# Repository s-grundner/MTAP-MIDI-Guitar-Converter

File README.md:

# [MTAP-MIDI-Guitar-Converter](http://www.htl-salzburg.ac.at/elektronik-technische-informatik-diplomarbeiten/1594.html) [DE]
<picture>
 <source media="(prefers-color-scheme: dark)" srcset="/documentation/images/MTAP-logo-weiss.png" align="right" width="450px"/>
 
</picture>

## Kurzberschreibung
Das vorliegende Projekt ermöglicht die Verwendung einer E-Gitarre als MIDI-Device. Das Gerät soll einzelne Noten und Akkorde zuverlässig mit möglichst geringer Latenz in das MIDI-Format umwandeln. Die MIDI-Signale werden an die USB-Schnittstelle eines PCs übertragen, von welchem die Signale beliebig interpretiert werden können.

## Vorhaben, Lösungsweg und Innovation
Virtuelle Instrumente sind in der modernen Musik-Produktion aufgrund ihrer Vielseitigkeit weit verbreitet. Das Projekt, ein Audiodaten-Verarbeitungssystem, macht es möglich, diese virtuellen Instrumente auch mit einer E-Gitarre zu spielen. Hierfür wird das analoge Audiosignal direkt von der Ausgangsbuchse der Gitarre abgegriffen, in MIDI-Noten umgewandelt und via USB an eine Digital Audio Workstation (DAW) übertragen.

Die Ein- und Ausgänge des Systems umfassen eine Micro-USB-Buchse und zwei Mono-Audio Buchsen. Die analogen Signale werden zunächst an einer der Buchsen abgegriffen, digitalisiert und von einem leistungsstarken 32-Bit Prozessor analysiert. Die Daten, die sich aus der Analyse ergeben, werden anschließend in das MIDI Format konvertiert und über die USB-Schnittstelle ausgegeben.

Der Vorteil des MIDI-Formats ist, dass es der Standard vieler Musikproduktionsumgebungen ist. In der DAW wird das MIDI-Signal als Note auf einem Klavier interpretiert, welches dann in beliebige virtuelle Instrumente eingespeist werden kann und somit einen benutzerdefinierten Ton abspielt.

### 3D Renderung der Platine

| Top-Seite | Bot-Seite |
|-|-|
|||

### Assemblierter Prototyp

|  |  |
|-|-|

## Mitwirkende
### Betreuer
[Prof. Dipl.-Ing. Siegbert Schrempf](https://www.linkedin.com/in/siegbert-schrempf-aa1189a)
### Entwickler
- [Simon Grundner](https://github.com/s-grundner)
- [Laurenz Hölzl](https://github.com/Laurenz03)
- [Daniel Bräumann](https://github.com/Hexewillfred)

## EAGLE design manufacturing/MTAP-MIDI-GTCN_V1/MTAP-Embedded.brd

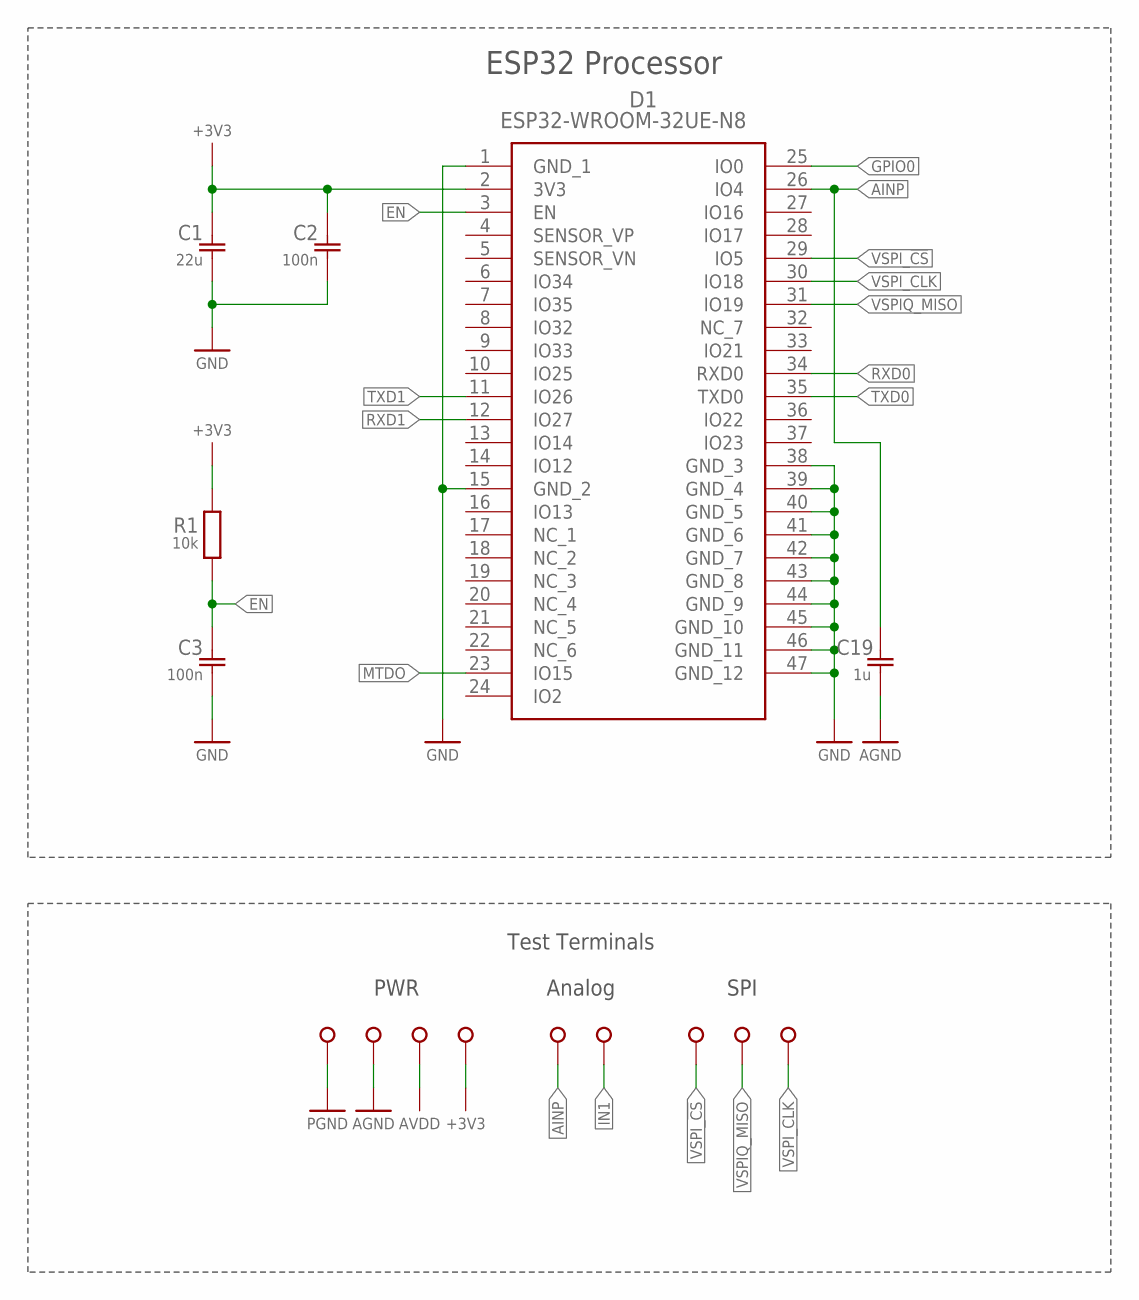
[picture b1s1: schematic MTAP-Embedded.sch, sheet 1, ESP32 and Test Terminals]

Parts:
3V3: SMD-TP; S2751-46R
AGND: SMD-TP; S2751-46R
AIN: SMD-TP; S2751-46R
AVDD: SMD-TP; S2751-46R
C1: 22u; C0805
C2, C3: 100n; C0805
C19: 1u; C0805
D1: ESP32-WROOM-32UE-N8; ESP32WROOM32UEN8
PGND: SMD-TP; S2751-46R
POST-AFE: SMD-TP; S2751-46R
R1: 10k; R0805
SPIQ: SMD-TP; S2751-46R
SPI_CLK: SMD-TP; S2751-46R
SPI_CS: SMD-TP; S2751-46R

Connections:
+3V3: 3V3.P$1, C1.1, C2.1, D1.2 (3V3), R1.2; also elsewhere on the board
AGND: AGND.P$1, C19.2; also elsewhere on the board
AINP: C19.1, D1.26 (IO4), POST-AFE.P$1; also elsewhere on the board
AVDD: AVDD.P$1; also elsewhere on the board
EN: C3.1, D1.3 (EN), R1.1; also elsewhere on the board
GND: C1.2, C2.2, C3.2, D1.1 (GND_1), D1.15 (GND_2), D1.38 (GND_3), D1.39 (GND_4), D1.40 (GND_5), D1.41 (GND_6), D1.42 (GND_7), D1.43 (GND_8), D1.44 (GND_9), D1.45 (GND_10), D1.46 (GND_11), D1.47 (GND_12); also elsewhere on the board
GPIO0: D1.25 (IO0); also elsewhere on the board
IN1: AIN.P$1; also elsewhere on the board
MTDO: D1.23 (IO15)
PGND: PGND.P$1; also elsewhere on the board
RXD0: D1.34 (RXD0); also elsewhere on the board
RXD1: D1.12 (IO27); also elsewhere on the board
TXD0: D1.35 (TXD0); also elsewhere on the board
TXD1: D1.11 (IO26); also elsewhere on the board
VSPIQ_MISO: D1.31 (IO19), SPIQ.P$1; also elsewhere on the board
VSPI_!CS: D1.29 (IO5), SPI_CS.P$1; also elsewhere on the board
VSPI_CLK: D1.30 (IO18), SPI_CLK.P$1; also elsewhere on the board

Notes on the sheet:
ESP32 Processor
PWR
Analog
SPI
Test Terminals

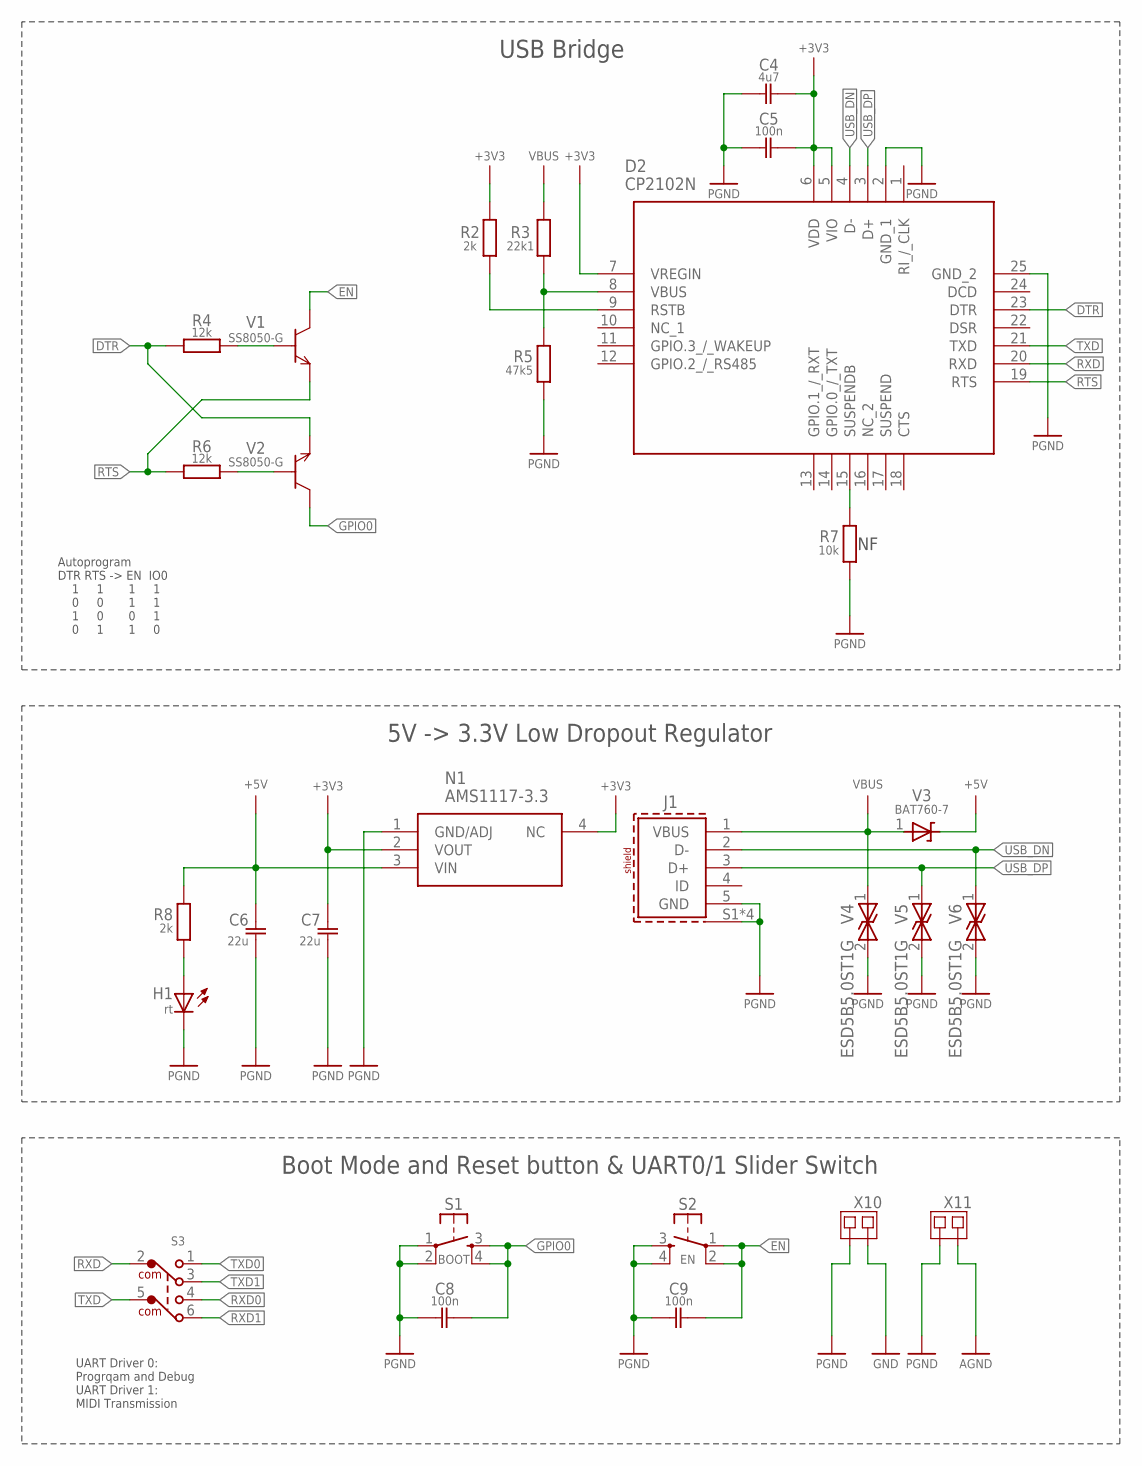
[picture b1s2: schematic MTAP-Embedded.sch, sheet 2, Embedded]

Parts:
C4: 4u7; C0805
C5, C8, C9: 100n; C0805
C6, C7: 22u; C0805
D2: CP2102N; QFN24
H1: rt; CHIP-LED0805
J1: 629105150521
N1: AMS1117-3.3; SOT229P700X180-4N
R2, R8: 2k; R0805
R3: 22k1; R0805
R4, R6: 12k; R0805
R5: 47k5; R0805
R7: 10k; R0805
S1: BOOT; WE_436331045822
S2: EN; WE_436331045822
S3: 452404020202
V1, V2: SS8050-G; SOT95P240X115-3N
V3: BAT760-7; SOD323
V4, V5, V6: ESD5B5.0ST1G; SOD523
X10, X11: 0R; MYLIB_SJ-SHORT

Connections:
+3V3: C4.1, C5.1, C7.1, D2.5 (VIO), D2.6 (VDD), D2.7 (VREGIN), N1.2 (VOUT), N1.4 (NC), R2.1; also elsewhere on the board
+5V: C6.1, N1.3 (VIN), R8.2, V3.2 (A)
AGND: X11.2; also elsewhere on the board
DTR: D2.23 (DTR), R4.1, V2.2 (E)
EN: C9.1, S2.1, S2.2 (P1), V1.3 (C); also elsewhere on the board
GND: X10.2; also elsewhere on the board
GPIO0: C8.1, S1.3 (S), S1.4 (S1), V2.3 (C); also elsewhere on the board
unnamed: H1.A, R8.1
unnamed: D2.8 (VBUS), R3.2, R5.2
unnamed: D2.15 (SUSPENDB), R7.2
unnamed: D2.9 (RSTB), R2.2
unnamed: R4.2, V1.1 (B)
unnamed: R6.2, V2.1 (B)
PGND: C4.2, C5.2, C6.2, C7.2, C8.2, C9.2, D2.2 (GND_1), D2.25 (GND_2), H1.C, J1.5 (GND), J1.S1 (SHIELD), J1.S2 (SHIELD), J1.S3 (SHIELD), J1.S4 (SHIELD), N1.1 (GND/ADJ), R5.1, R7.1, S1.1, S1.2 (P1), S2.3 (S), S2.4 (S1), V4.2, V5.2, V6.2, X10.1, X11.1; also elsewhere on the board
RTS: D2.19 (RTS), R6.1, V1.2 (E)
RXD: D2.20 (RXD), S3.2 (COM)
RXD0: S3.4; also elsewhere on the board
RXD1: S3.6; also elsewhere on the board
TXD: D2.21 (TXD), S3.5 (COM1)
TXD0: S3.1; also elsewhere on the board
TXD1: S3.3; also elsewhere on the board
USB_DN: D2.4 (D-), J1.2 (D-), V6.1
USB_DP: D2.3 (D+), J1.3 (D+), V5.1
VBUS: J1.1 (VBUS), R3.1, V3.1 (K), V4.1

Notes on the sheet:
UART Driver 0: Progrqam and Debug UART Driver 1: MIDI Transmission
USB Bridge
5V -> 3.3V Low Dropout Regulator
Boot Mode and Reset button & UART0/1 Slider Switch
Autoprogram DTR RTS -> EN IO0 1 1 1 1 0 0 1 1 1 0 0 1 0 1 1 0

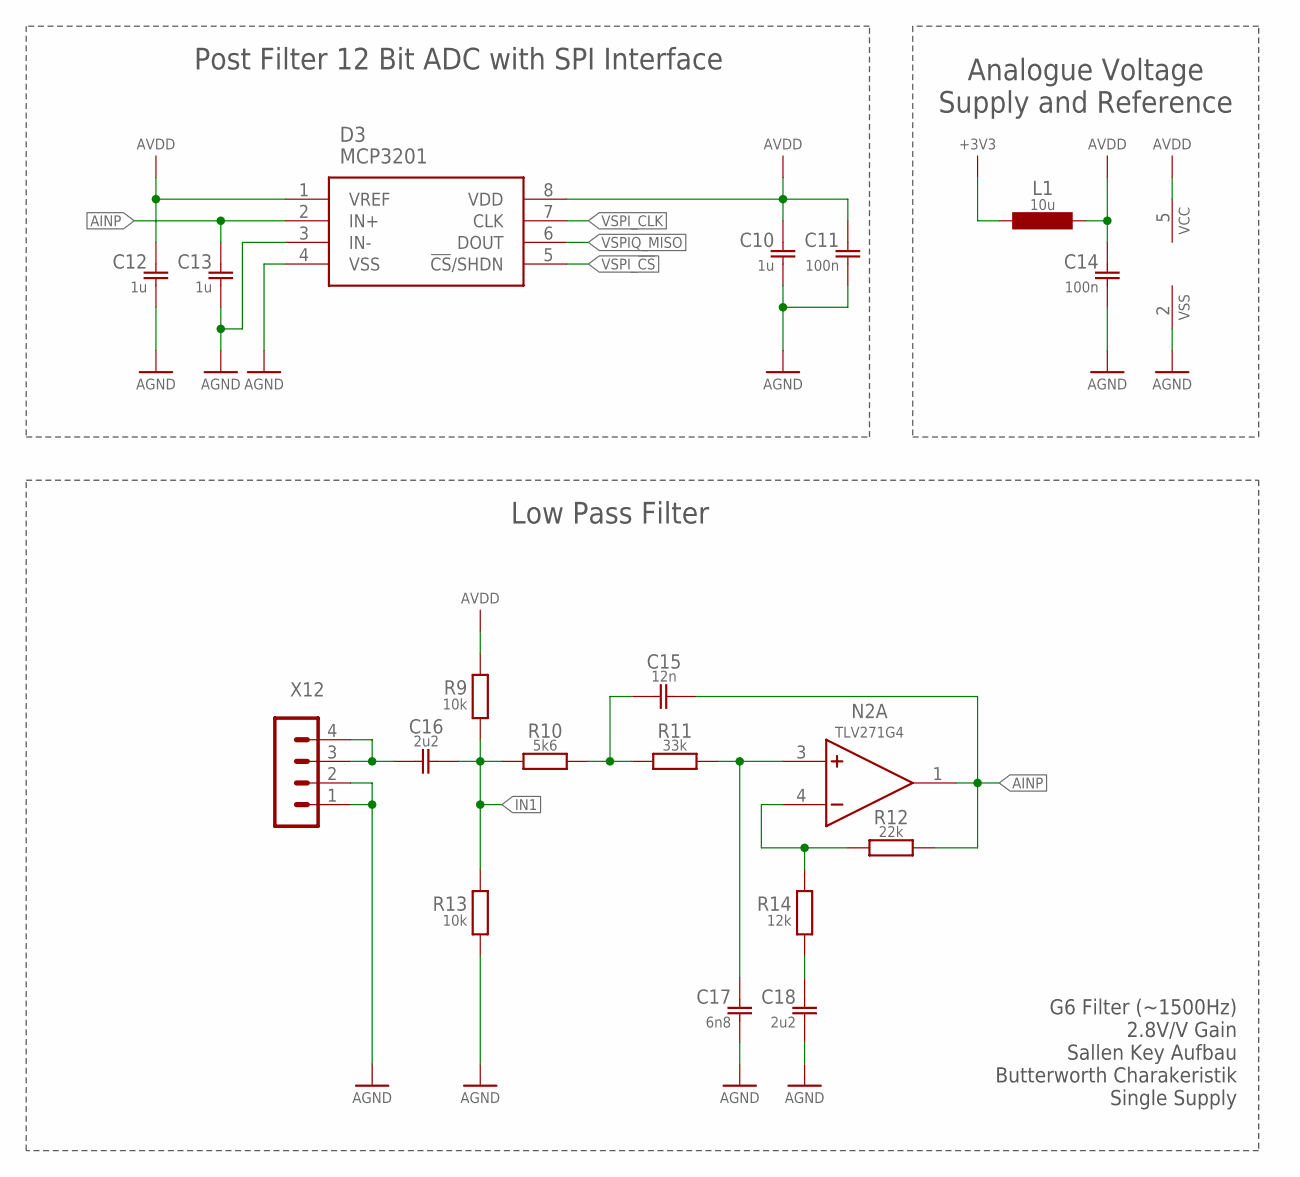
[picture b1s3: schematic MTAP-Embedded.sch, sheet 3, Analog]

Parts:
C10, C12, C13: 1u; C0805
C11, C14: 100n; C0805
C15: 12n; C0805
C16, C18: 2u2; C0805
C17: 6n8; C0805
D3: MCP3201; SOIC127P600X175-8N
L1: 10u; MYLIB_L3216C
N2: TLV271G4; SOT95P280X145-5N
R9, R13: 10k; R0805
R10: 5k6; R0805
R11: 33k; R0805
R12: 22k; R0805
R14: 12k; R0805
X12: MA04-1

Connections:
+3V3: L1.1; also elsewhere on the board
AGND: C10.2, C11.2, C12.2, C13.2, C14.2, C17.2, C18.2, D3.3 (IN-), D3.4 (VSS), N2.2 (VSS), R13.1, X12.1, X12.2; also elsewhere on the board
AINP: C13.1, C15.1, D3.2 (IN+), N2.1 (O), R12.2; also elsewhere on the board
AVDD: C10.1, C11.1, C12.1, C14.1, D3.1 (VREF), D3.8 (VDD), L1.2, N2.5 (VCC), R9.2; also elsewhere on the board
IN0: C16.2, X12.3, X12.4
IN1: C16.1, R9.1, R10.1, R13.2; also elsewhere on the board
unnamed: N2.4 (N), R12.1, R14.2
unnamed: C18.1, R14.1
unnamed: C17.1, N2.3, R11.2
unnamed: C15.2, R10.2, R11.1
VSPIQ_MISO: D3.6 (DOUT); also elsewhere on the board
VSPI_!CS: D3.5 (!CS!/SHDN); also elsewhere on the board
VSPI_CLK: D3.7 (CLK); also elsewhere on the board

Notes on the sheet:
Post Filter 12 Bit ADC with SPI Interface
Analogue Voltage Supply and Reference
Low Pass Filter
G6 Filter (~1500Hz) 2.8V/V Gain Sallen Key Aufbau Butterworth Charakeristik Single Supply

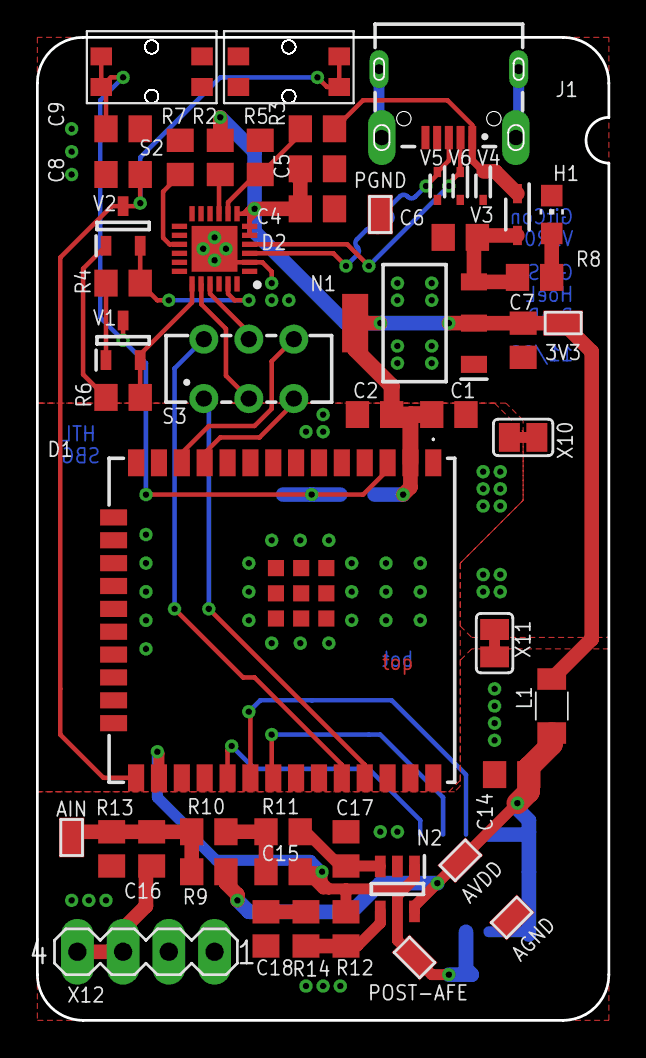
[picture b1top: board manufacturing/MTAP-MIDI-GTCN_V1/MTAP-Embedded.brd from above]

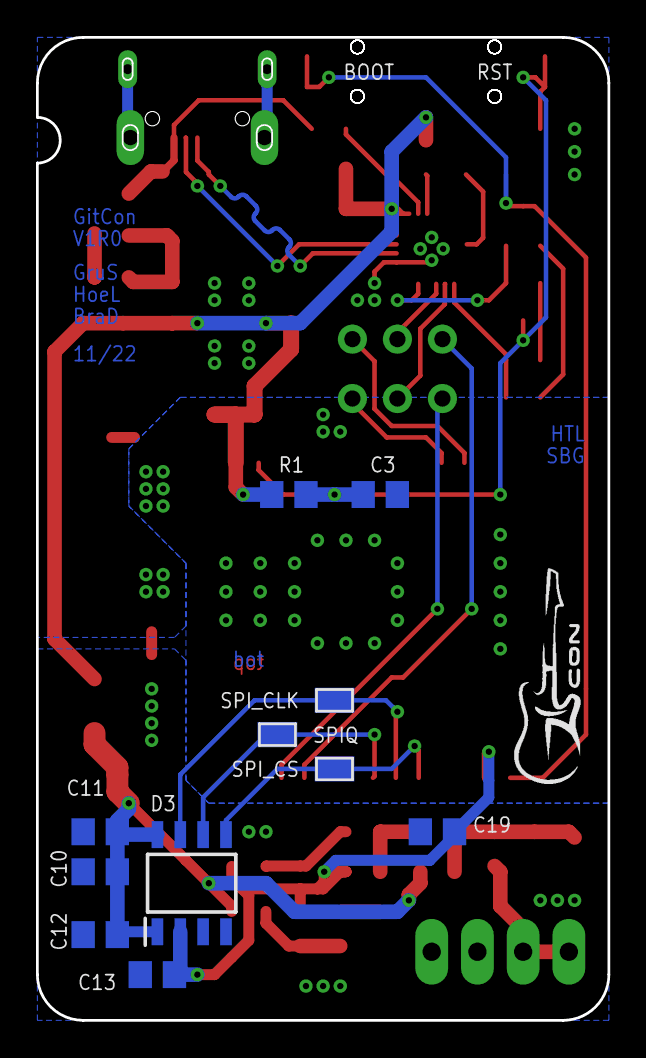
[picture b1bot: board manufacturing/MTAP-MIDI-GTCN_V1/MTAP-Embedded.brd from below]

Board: 2 copper layers, 31.8 x 54.6 mm, 64 parts (11 on the bottom side), 35 nets.

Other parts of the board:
FABRICATION: FABRIACTION
MEASURE: MEASURE

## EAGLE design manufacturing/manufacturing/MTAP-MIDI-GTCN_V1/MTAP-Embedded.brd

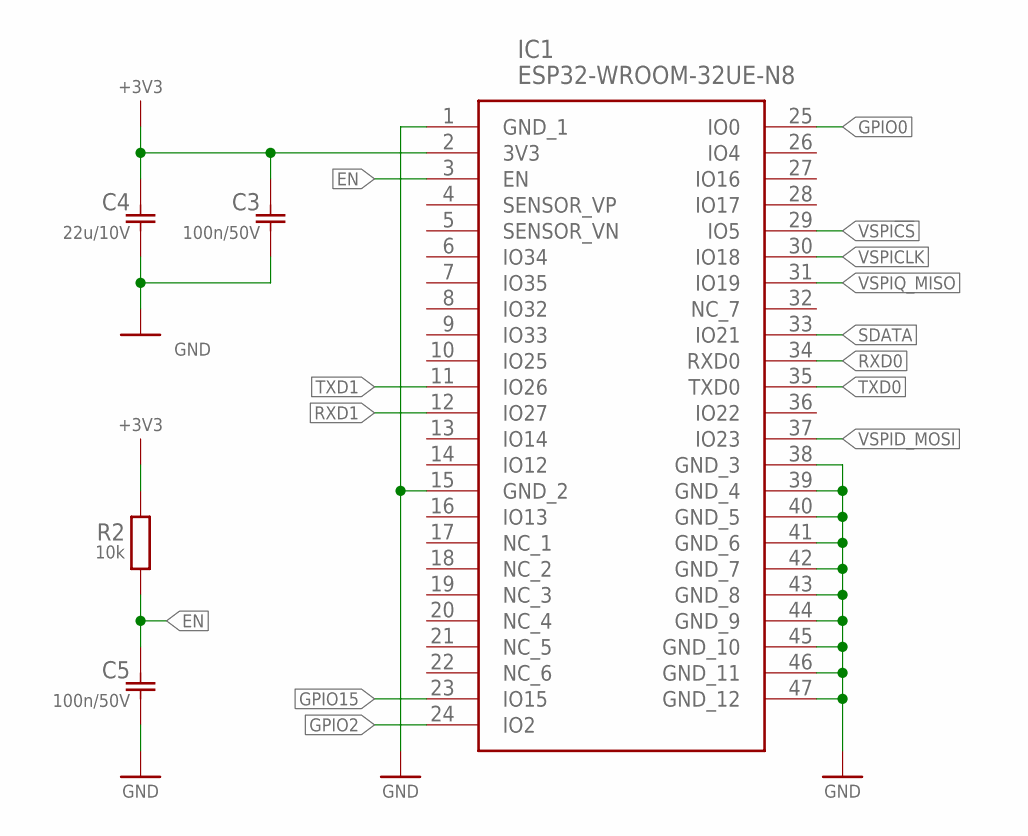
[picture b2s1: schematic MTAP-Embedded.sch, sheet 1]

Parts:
C3, C5: 100n/50V; C0805
C4: 22u/10V; C0805
IC1: ESP32-WROOM-32UE-N8; ESP32WROOM32UEN8
R2: 10k; R0805

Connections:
+3V3: C3.1, C4.1, IC1.2 (3V3), R2.2; also elsewhere on the board
EN: C5.1, IC1.3 (EN), R2.1; also elsewhere on the board
GND: C3.2, C4.2, C5.2, IC1.1 (GND_1), IC1.15 (GND_2), IC1.38 (GND_3), IC1.39 (GND_4), IC1.40 (GND_5), IC1.41 (GND_6), IC1.42 (GND_7), IC1.43 (GND_8), IC1.44 (GND_9), IC1.45 (GND_10), IC1.46 (GND_11), IC1.47 (GND_12); also elsewhere on the board
GPIO0: IC1.25 (IO0); also elsewhere on the board
GPIO2: IC1.24 (IO2)
GPIO15: IC1.23 (IO15)
RXD0: IC1.34 (RXD0); also elsewhere on the board
RXD1: IC1.12 (IO27); also elsewhere on the board
SDATA: IC1.33 (IO21)
TXD0: IC1.35 (TXD0); also elsewhere on the board
TXD1: IC1.11 (IO26); also elsewhere on the board
VSPI!CS: IC1.29 (IO5); also elsewhere on the board
VSPICLK: IC1.30 (IO18); also elsewhere on the board
VSPID_MOSI: IC1.37 (IO23)
VSPIQ_MISO: IC1.31 (IO19); also elsewhere on the board

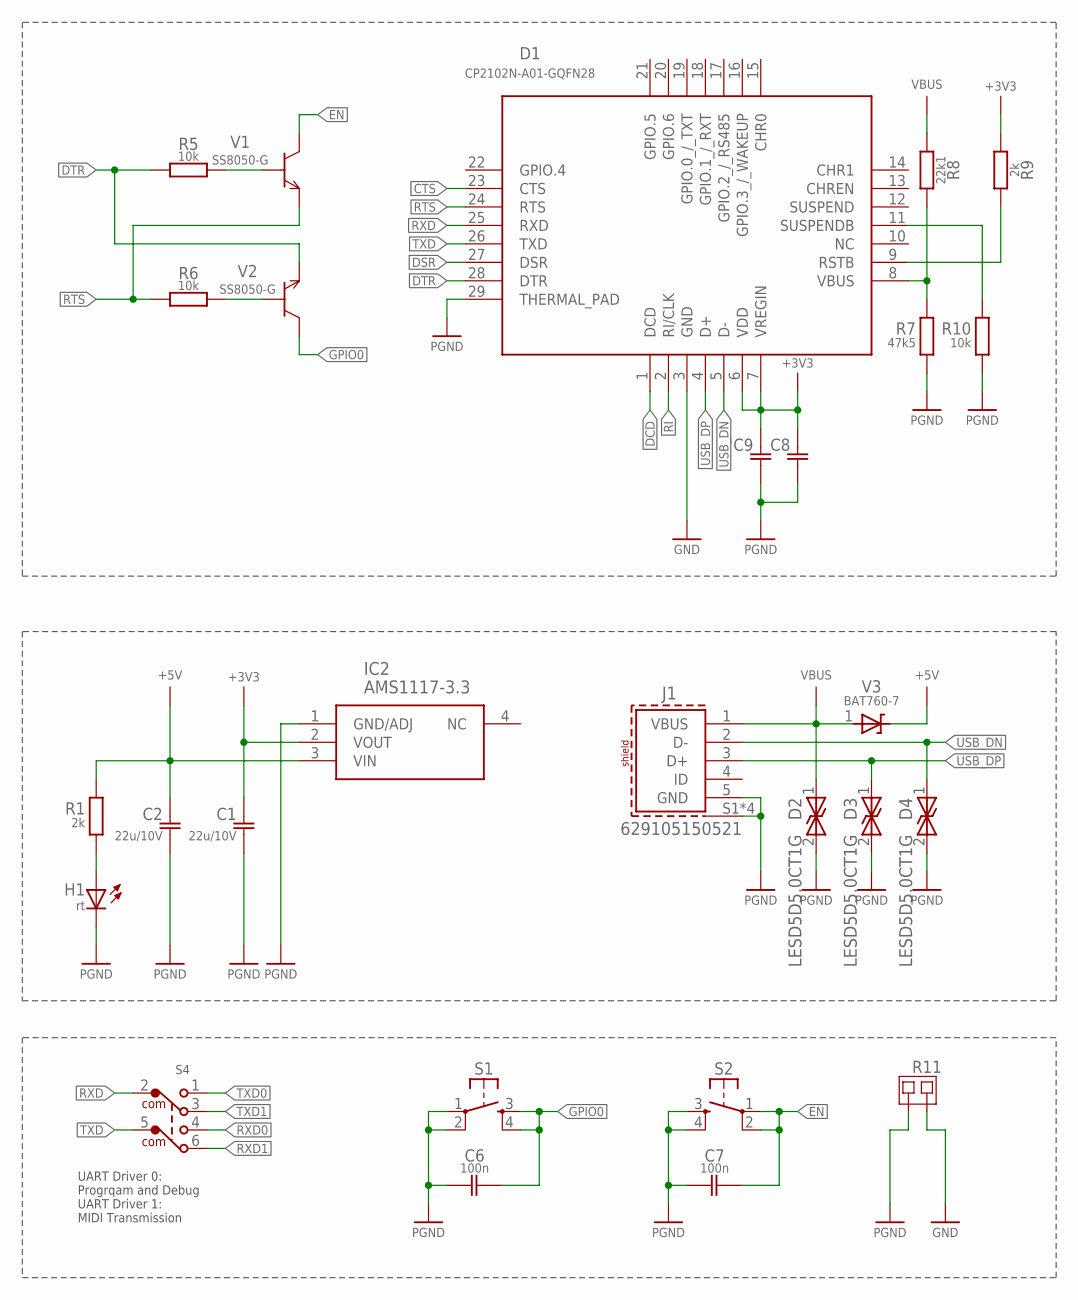
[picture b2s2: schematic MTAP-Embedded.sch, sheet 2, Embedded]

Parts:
C1, C2: 22u/10V; C0805
C6, C7: 100n; C0805
C8, C9: C-EUC0805; C0805
D1: CP2102N-A01-GQFN28; QFN28
D2, D3, D4: LESD5D5.0CT1G; SOD523
H1: rt; CHIP-LED0805
IC2: AMS1117-3.3; SOT229P700X180-4N
J1: 629105150521
R1, R9: 2k; R0805
R5, R6, R10: 10k; R0805
R7: 47k5; R0805
R8: 22k1; R0805
R11: 0R; MYLIB_SJ-SHORT
S1, S2: TASTE10XXWE; WE_436331045822
S4: 452404020202
V1, V2: SS8050-G; SOT95P240X115-3N
V3: BAT760-7; SOD323

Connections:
+3V3: C1.1, C8.1, C9.1, D1.6 (VDD), D1.7 (VREGIN), IC2.2 (VOUT), R9.1; also elsewhere on the board
+5V: C2.1, IC2.3 (VIN), R1.2, V3.2 (A)
CTS: D1.23 (CTS)
DCD: D1.1 (DCD)
DSR: D1.27 (DSR)
DTR: D1.28 (DTR), R5.1, V2.2 (E)
EN: C7.1, S2.1, S2.2 (P1), V1.3 (C); also elsewhere on the board
GND: D1.3 (GND), R11.2; also elsewhere on the board
GPIO0: C6.1, S1.3 (S), S1.4 (S1), V2.3 (C); also elsewhere on the board
unnamed: H1.A, R1.1
unnamed: D1.8 (VBUS), R7.2, R8.2
unnamed: D1.11 (SUSPENDB), R10.2
unnamed: D1.9 (RSTB), R9.2
unnamed: R5.2, V1.1 (B)
unnamed: R6.2, V2.1 (B)
PGND: C1.2, C2.2, C6.2, C7.2, C8.2, C9.2, D1.29 (THERMAL_PAD), D2.2, D3.2, D4.2, H1.C, IC2.1 (GND/ADJ), J1.5 (GND), J1.S1 (SHIELD), J1.S2 (SHIELD), J1.S3 (SHIELD), J1.S4 (SHIELD), R7.1, R10.1, R11.1, S1.1, S1.2 (P1), S2.3 (S), S2.4 (S1)
RI: D1.2 (RI/CLK)
RTS: D1.24 (RTS), R6.1, V1.2 (E)
RXD: D1.25 (RXD), S4.2 (COM)
RXD0: S4.4; also elsewhere on the board
RXD1: S4.6; also elsewhere on the board
TXD: D1.26 (TXD), S4.5 (COM1)
TXD0: S4.1; also elsewhere on the board
TXD1: S4.3; also elsewhere on the board
USB_DN: D1.5 (D-), D4.1, J1.2 (D-)
USB_DP: D1.4 (D+), D3.1, J1.3 (D+)
VBUS: D2.1, J1.1 (VBUS), R8.1, V3.1 (K)

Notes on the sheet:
UART Driver 0: Progrqam and Debug UART Driver 1: MIDI Transmission

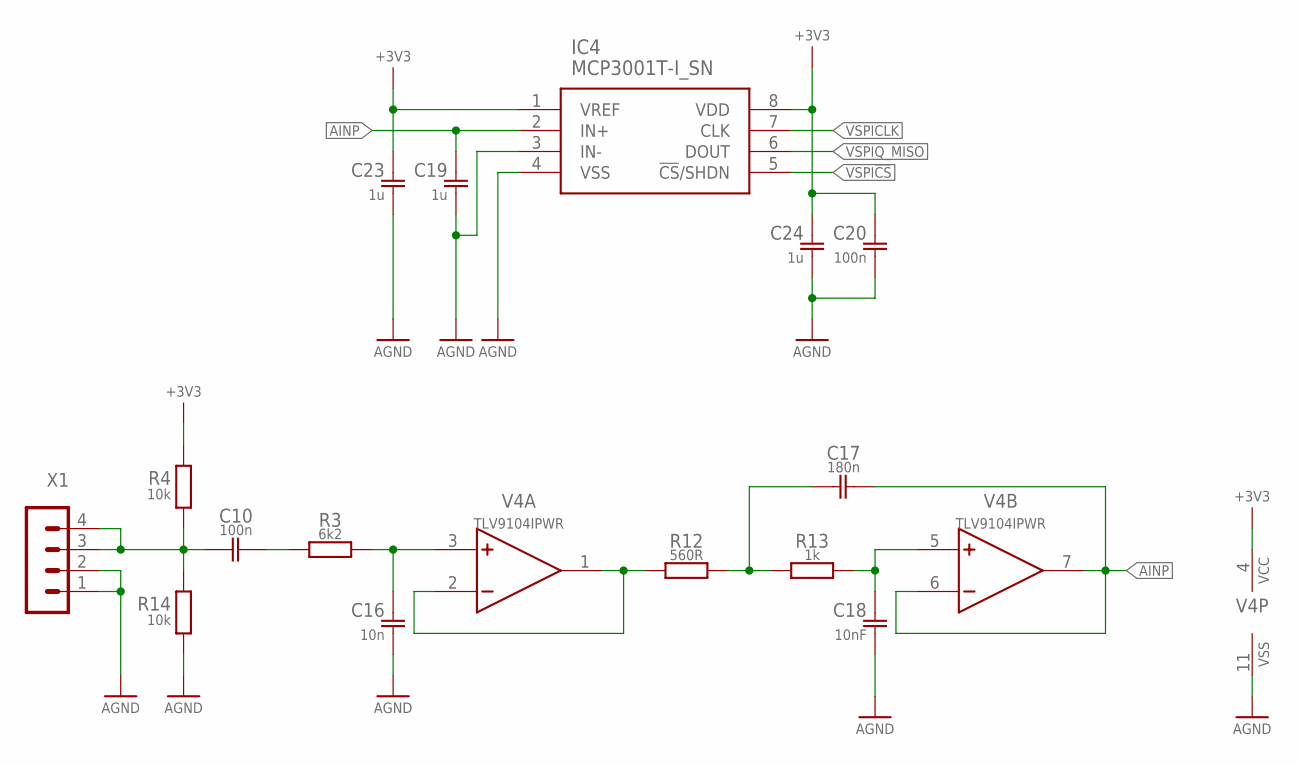
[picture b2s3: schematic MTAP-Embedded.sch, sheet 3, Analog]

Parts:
C10, C20: 100n; C0805
C16: 10n; C0805
C17: 180n; C0805
C18: 10nF; C0805
C19, C23, C24: 1u; C0805
IC4: MCP3001T-I_SN; SOIC127P600X175-8N
R3: 6k2; R0805
R4, R14: 10k; R0805
R12: 560R; R0805
R13: 1k; R0805
V4: TLV9104IPWR; SOP65P640X120-14N
X1: MA04-1

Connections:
+3V3: C20.1, C23.1, C24.1, IC4.1 (VREF), IC4.8 (VDD), R4.2, V4.4 (VCC); also elsewhere on the board
AGND: C16.2, C18.2, C19.2, C20.2, C23.2, C24.2, IC4.3 (IN-), IC4.4 (VSS), R14.1, V4.11 (VSS), X1.1, X1.2
AINP: C17.1, C19.1, IC4.2 (IN+), V4.6 (N), V4.7 (O)
unnamed: R12.1, V4.1 (O), V4.2 (N)
unnamed: C16.1, R3.2, V4.3
unnamed: C10.1, R3.1
unnamed: C17.2, R12.2, R13.1
unnamed: C18.1, R13.2, V4.5
unnamed: C10.2, R4.1, R14.2, X1.3, X1.4
VSPI!CS: IC4.5 (!CS!/SHDN); also elsewhere on the board
VSPICLK: IC4.7 (CLK); also elsewhere on the board
VSPIQ_MISO: IC4.6 (DOUT); also elsewhere on the board

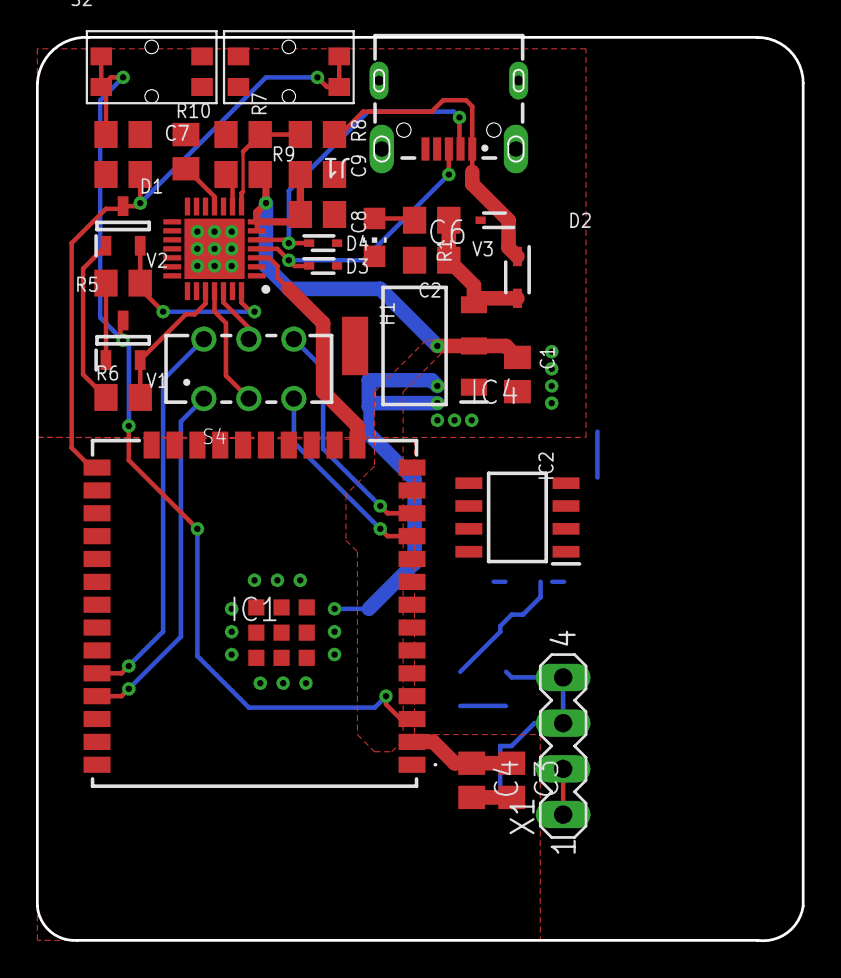
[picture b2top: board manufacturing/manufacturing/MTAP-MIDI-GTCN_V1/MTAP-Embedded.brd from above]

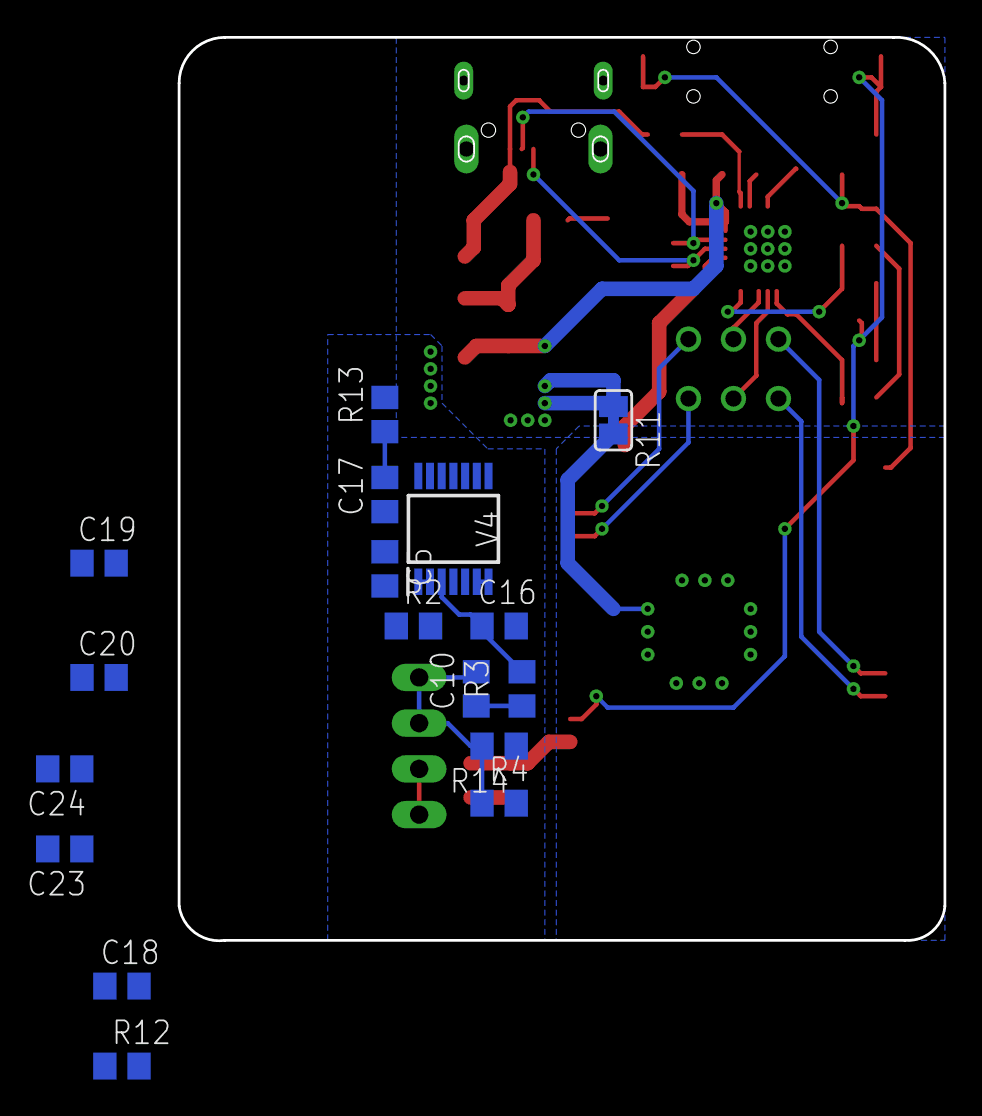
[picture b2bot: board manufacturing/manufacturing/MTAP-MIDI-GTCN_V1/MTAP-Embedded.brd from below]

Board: 2 copper layers, 42.5 x 50.2 mm, 48 parts (17 on the bottom side), 34 nets.

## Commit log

2022-09-28 Planung
    Projektplanung
2022-10-04 upd DA
2022-10-11 sync Di 11.10.2022
2022-10-12 updated folder structure
2022-10-12 upd folders
2022-10-12 added badges to readme
2022-10-18 upd bsb
2022-10-18 upd asset folders
2022-10-19 typos
2022-10-20 upd schematic
2022-10-22 added Logo and tested ESP footprints
    schematic for ESP complete
    except values
2022-10-22 upd logo
2022-10-25 upd PPL
2022-10-25 firmware init
2022-10-25 c properties
2022-10-25 upd Embedded
2022-10-26 upd embedded schematic
2022-10-26 upd board
    upd pcb
    added Kostenrechnung
    upd PPL-GruS
2022-10-28 Update Embedded
    added PCM ADC to PCB
2022-10-28 Create LICENSE
2022-11-03 Upd pcb
2022-11-03 upd MIDI testing
2022-11-04 included midisoftware and drivers for PC
2022-11-04 pre Filter Design
    added Reports for Filter Design
2022-11-04 upd analog board
2022-11-04 upd pcb
    added filter to schematic
2022-11-05 ADC unavailable PCB upd
    #3 Issued.
    Last Push before replacement.
2022-11-05 New Layout
2022-11-06 upd board
2022-11-06 Upd PCB
    Finished new Board essentials
    Analog parts excluded and yet to be implemented
2022-11-07 adp adc #3 pcb
2022-11-07 upd pcb analog
    new filter
    new ADC
2022-11-08 upd analog
2022-11-08 upd schematic to fix adc problem
2022-11-08 upd to new adc
    filter neu dimensionieren
2022-11-11 update analogue process chain onboard
2022-11-12 finished PCB
    issues with filter circuit only works wit dual supply. negative voltage may be needed
2022-11-13 Update Filter
    Filter may need negative voltage
    Develop Filter which keeps the offset
2022-11-13 upd doc structure and organisational stuff
2022-11-14 upd schematic values
2022-11-15 UPd PCB
    Added new Filter to board
2022-11-15 upd Di 20221115
2022-11-17 documentation update
    Added git clean script
    updated board
    added bulletpoints to LH and PH
2022-11-18 update boasrd
    pre PR commit
2022-11-18 upd gitignore
2022-11-18 cleanup
2022-11-18 clean for PR
2022-11-18 added docs
2022-11-18 upd brd
2022-11-20 Finished PCB
    - Added Test Terminals
    - Finalised Filter Design
    - Added all 3d models and created external Fusion 360 Project
    - Updated Filter simulation draft
2022-11-20 upd STL
    added Reference for docs
2022-11-22 Jugend Innovativ
2022-11-22 basic fft function testing
2022-11-23 fft debugging
2022-11-30 upd schematic
    home office push
2022-11-30 Frequency & keyNR computation
2022-11-30 JI-anmeldung
    docs update
2022-11-30 Software-Doku
2022-11-30 up docs
2022-12-14 upd logo and poster
2022-12-14 upd images
2022-12-14 upd SWD
2022-12-15 upd poster
2022-12-15 added spl images
2022-12-15 move bsb
2022-12-17 upd Brd
    - Power Section
    - Diff Pairs
    PR Ready
2022-12-17 Finalised Board
    added missing connections to USB Bridge.
    Added 3d Images to docs
2022-12-19 added gif
2022-12-19 upd pptx
2022-12-19 upd docs and pptx
2022-12-20 pptx upd
2022-12-20 doku
2022-12-20 vault backup: 2022-12-20 11:52:24
2022-12-20 gitignore
2022-12-20 vault backup: 2022-12-20 12:02:51
2022-12-21 python tools
2022-12-21 updated python tools
2022-12-21 upd logo and adc testing prg
2022-12-22 poster neu und bauteile beim poer gfladdert
2022-12-22 upd adc source
2022-12-23 upd adc firmware
2022-12-23 upd midi firmware
2022-12-26 midi functional test
2022-12-26 Filter Ausmessung
2022-12-27 upd midi serial
2022-12-27 upd board and images
    added internal adc connection
2022-12-29 placed pcb order
2023-01-09 upd doc names
2023-01-09 upd midi
2023-01-09 tests
2023-01-09 test
2023-01-10 finished enhancement and ready to PR
2023-01-10 added midi utils for configuring messages
2023-01-10 python refinement
2023-01-10 fixed midi data transmission windup
2023-01-10 converted fft to midi Testing 1
2023-01-10 clean
2023-01-11 quick fix
2023-01-11 midi dip keyboard
2023-01-11 MIDI dip switch showcase
2023-01-11 pre-PR
2023-01-12 cleanup (pre dma testing)
2023-01-12 upd dma testing
2023-01-12 cleaned up code before showcase
2023-01-12 i2s sampler lib
2023-01-12 dma sampling working (ready for PR)
2023-01-13 Unified buffer size and sample rate
    showcase ready
2023-01-13 upd config
2023-01-14 fixed sampled data representation and programmed mcp sampler
    # data is now prebresentated in 12 bit format
    2 samples were combined into one 28bit value due to wrong data dype
    # mcp
    mcp sample implemented
    no system tests were done
2023-01-15 implemented fft in code
    non functional yet
2023-01-28 buffer gen for fft
    still not functional
2023-01-28 upd docs
2023-01-30 vault backup: 2023-01-30 07:58:26
2023-01-30 vault backup: 2023-01-30 08:08:26
2023-01-30 upd sw docs
2023-01-31 ref pflichtenheft
2023-02-07 1st iteration
2023-02-07 rework of DSP
2023-02-07 backtrace monitor
2023-02-07 bool note on off
2023-02-07 upd fehlererfassung PR ready
2023-02-08 cleaned up code
    added credits
    optimized nesting a bit
2023-02-10 upd readme images
2023-02-10 upd images and gitignore
2023-02-14 upd fehler erfassung
2023-02-14 vault backup: 2023-02-14 12:58:21
2023-02-14 vault backup: 2023-02-14 13:18:38 from
2023-02-14 vault backup: 2023-02-14 13:55:05 from
2023-02-14 vault backup: 2023-02-14 14:26:04 from
2023-02-14 vault backup: 2023-02-14 18:55:46 from
2023-02-14 vault backup: 2023-02-14 21:05:56 from
2023-02-14 vault backup: 2023-02-14 23:49:24 from
2023-02-16 upd docs
    added new Images
    added Bibliography and listed references
    [Scribbr](https://www.scribbr.de/zitieren/generator/ordnern/4Rp5YO6sPAOxOdqrDjw8E8/listen/7mXKVOOMal9hnskpYK4qol/)
2023-02-16 upd doc structure + backup
2023-02-20 git clean
2023-02-20 vault backup: 2023-02-20 21:38:23 from
2023-02-21 magnitude threshold & only deepest note check
2023-02-21 magnitude threshold & only deepest note check MIDI
2023-02-21 added processed-data path to midi-testing
2023-02-21 corrected gpio pins in config for midi rxtx
2023-02-21 upd midi q
2023-03-06 upd website images
2023-03-07 fixed allocation error
2023-03-07 enabled monitor
2023-03-08 midi datastream from sample
    converted single guitar sample to midi datastream
    Can be read in Ableton Live 11
2023-03-08 added midi unit test
    - midi blink
    - midi pitchbend
    - both combined
2023-03-08 saved unit-test result in ableton
2023-03-08 updated doxygen docs
2023-03-08 Create Doxyfile
2023-03-10 upd reference
2023-03-12 renamed project to Gitcon_Driver
2023-03-12 deleted Obsolete Files
    MIDI_Testing is now a unit test of the Gitcon_Driver
    The Project has been deleted
2023-03-13 upd docu comments
2023-03-16 Create test_fft.c
    Added fft unit test
2023-03-16 upd unittests
2023-03-21 added image
    ADC fail image
2023-03-21 live sampling
    approximate note is being detected and converted into a midi note which is then transmitted to the DAW
    Issues:
    - MIDI notes always on max velocity
    - precision is slightly off
2023-03-21 upd live sampling
2023-03-22 fft now delivers midi note with velocity
2023-03-22 reframing fft
2023-03-23 small refactor
2023-03-26 upd documentation
    upd doc comments
2023-03-26 run doxygen
2023-03-26 upd refman
2023-03-27 upd FRM
2023-03-27 upd tft display modules
2023-03-27 upd Attachments
2023-03-29 upd audio buffer alignment
2023-03-29 note detectoin more accurate
2023-03-30 Gantt
2023-03-30 GANT HOEL
2023-03-30 gant final hoel
2023-03-30 Begleitprotokoll und Gantt
2023-03-31 pre deadline
2023-03-31 upd test data
2023-03-31 Update issue templates
2023-03-31 DA export
2023-04-20 update case and images
2023-04-20 upd cad added stl
2023-05-11 druck doks
2023-05-11 --- REVIEW KONFORM ---
    Sensitivität adjustiert
2023-05-11 --- REVIEW KONFORM + ---
    so guht wars noch nie
2023-05-23 Presentations
2023-06-01 pres images
2023-07-15 rm org
2023-07-20 cleaned includes
2023-07-23 small asthetic changes
2023-07-30 upd library opacity
2023-07-30 updated code opacity
2023-07-31 upd mcp lib
2023-07-31 upd formatting
2023-07-31 upd code opacity
2023-12-25 Sim updated

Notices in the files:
parts and their libraries:
Wurth_Connectors_WR-USB: Copyright: Würth Elektronik
